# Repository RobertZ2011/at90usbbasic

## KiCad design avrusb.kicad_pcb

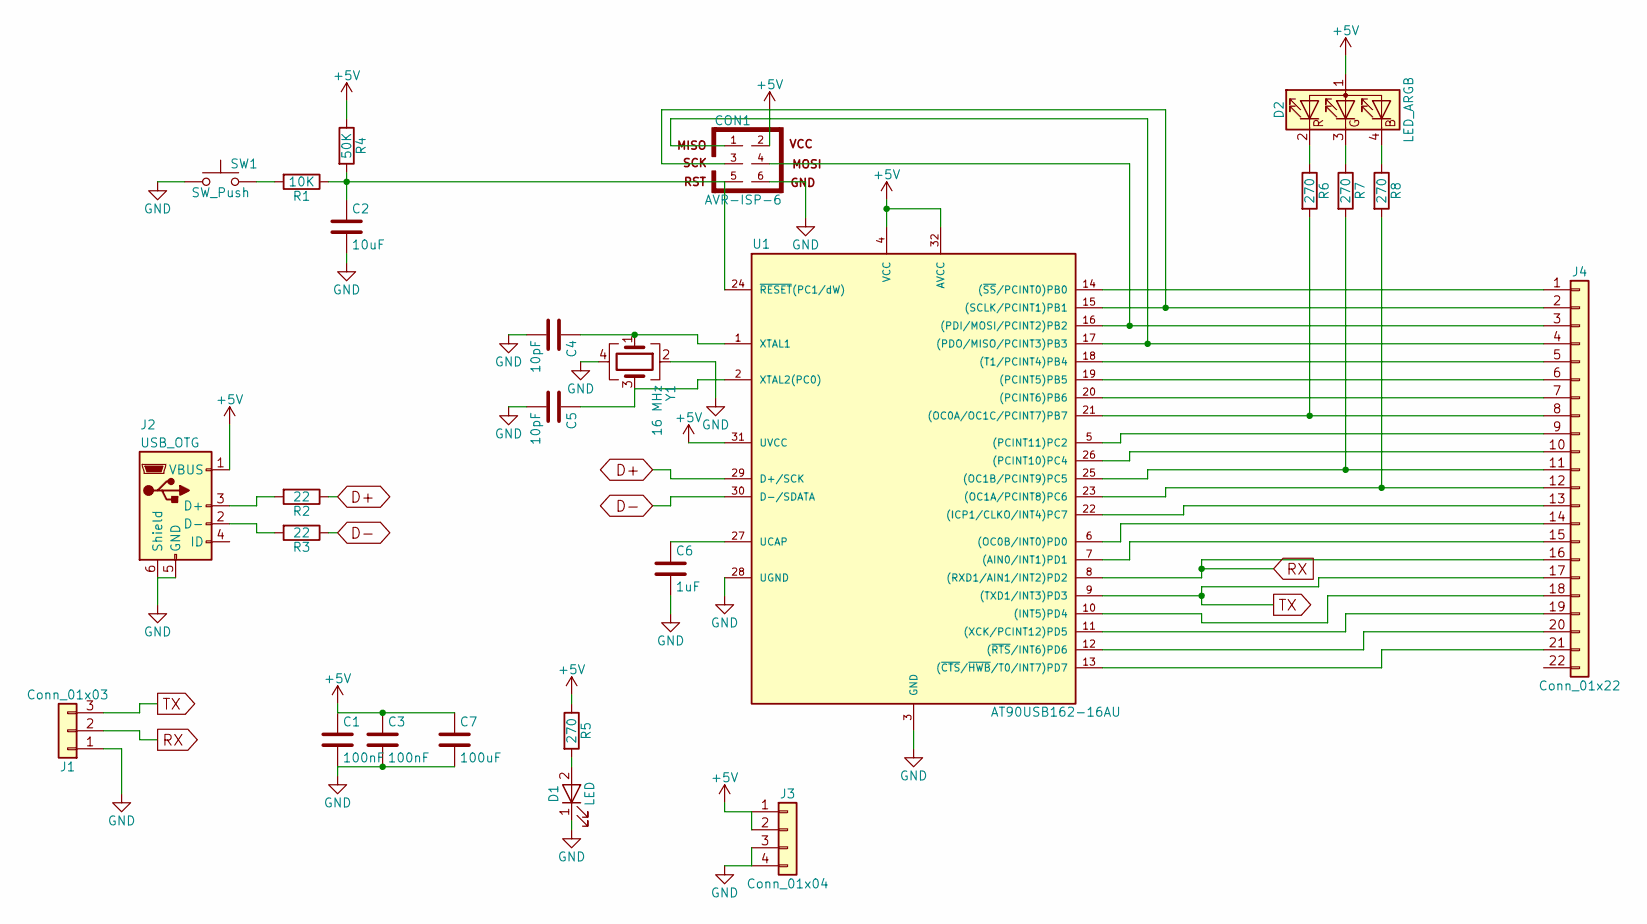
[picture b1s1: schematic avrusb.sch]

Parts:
C1, C3: 100nF; C_0805_HandSoldering
C2: 10uF; C_1206_HandSoldering
C4, C5: 10pF; C_0805_HandSoldering
C6: 1uF; C_1206_HandSoldering
C7: 100uF; CP_Elec_5x5.3
CON1: AVR-ISP-6; Pin_Header_Straight_2x03_Pitch2.54mm
D1: LED; LED_0805_HandSoldering
D2: LED_ARGB; LED_Cree-PLCC4_3.2x2.8mm_CCW
J1: Conn_01x03; Pin_Header_Straight_1x03_Pitch2.54mm
J2: USB_OTG; USB_Micro-B_Molex-105017-0001
J3: Conn_01x04; Pin_Header_Straight_1x04_Pitch2.54mm
J4: Conn_01x22; Pin_Header_Straight_2x11_Pitch2.54mm
R1: 10K; R_0805_HandSoldering
R2, R3: 22; R_0805_HandSoldering
R4: 50K; R_0805_HandSoldering
R5, R6, R7, R8: 270; R_0805_HandSoldering
SW1: SW_Push; SW_SPST_B3S-1000
U1: AT90USB162-16AU; TQFP-32_7x7mm_Pitch0.8mm
Y1: 16 MHz; Crystal_SMD_3225-4pin_3.2x2.5mm_HandSoldering

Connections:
D+: R2.1, U1.29 (D+/SCK)
D-: R3.1, U1.30 (D-/SDATA)
GND: C1.2, C2.2, C3.2, C4.2, C5.2, C6.2, C7.2, CON1.6, D1.1 (K), J1.1, J2.5 (GND), J2.6 (Shield), J3.3, J3.4, SW1.1, U1.3 (GND), U1.28 (UGND), Y1.2, Y1.4
unnamed: C2.1, CON1.5, R1.1, R4.2, U1.24 (~RESET~(PC1/dW))
unnamed: C4.1, U1.1 (XTAL1), Y1.1
unnamed: C5.1, U1.2 (XTAL2(PC0)), Y1.3
unnamed: C6.1, U1.27 (UCAP)
unnamed: CON1.1, J4.4, U1.17 ((PDO/MISO/PCINT3)PB3)
unnamed: CON1.4, J4.3, U1.16 ((PDI/MOSI/PCINT2)PB2)
unnamed: D1.2 (A), R5.2
unnamed: D2.2 (RK), R6.1
unnamed: D2.3 (GK), R7.1
unnamed: D2.4 (BK), R8.1
unnamed: J2.2 (D-), R3.2
unnamed: J2.3 (D+), R2.2
unnamed: J4.1, U1.14 ((~SS~/PCINT0)PB0)
unnamed: J4.5, U1.18 ((T1/PCINT4)PB4)
unnamed: J4.6, U1.19 ((PCINT5)PB5)
unnamed: J4.7, U1.20 ((PCINT6)PB6)
unnamed: J4.8, R6.2, U1.21 ((OC0A/OC1C/PCINT7)PB7)
unnamed: J4.9, U1.5 ((PCINT11)PC2)
unnamed: J4.10, U1.26 ((PCINT10)PC4)
unnamed: J4.11, R7.2, U1.25 ((OC1B/PCINT9)PC5)
unnamed: J4.12, R8.2, U1.23 ((OC1A/PCINT8)PC6)
unnamed: J4.13, U1.22 ((ICP1/CLKO/INT4)PC7)
unnamed: J4.14, U1.6 ((OC0B/INT0)PD0)
unnamed: J4.15, U1.7 ((AIN0/INT1)PD1)
unnamed: J4.18, U1.10 ((INT5)PD4)
unnamed: J4.19, U1.11 ((XCK/PCINT12)PD5)
unnamed: J4.20, U1.12 ((~RTS~/INT6)PD6)
unnamed: J4.21, U1.13 ((~CTS~/~HWB~/T0/INT7)PD7)
unnamed: R1.2, SW1.2
RX: J1.2, J4.16, U1.8 ((RXD1/AIN1/INT2)PD2)
TX: J1.3, J4.17, U1.9 ((TXD1/INT3)PD3)

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
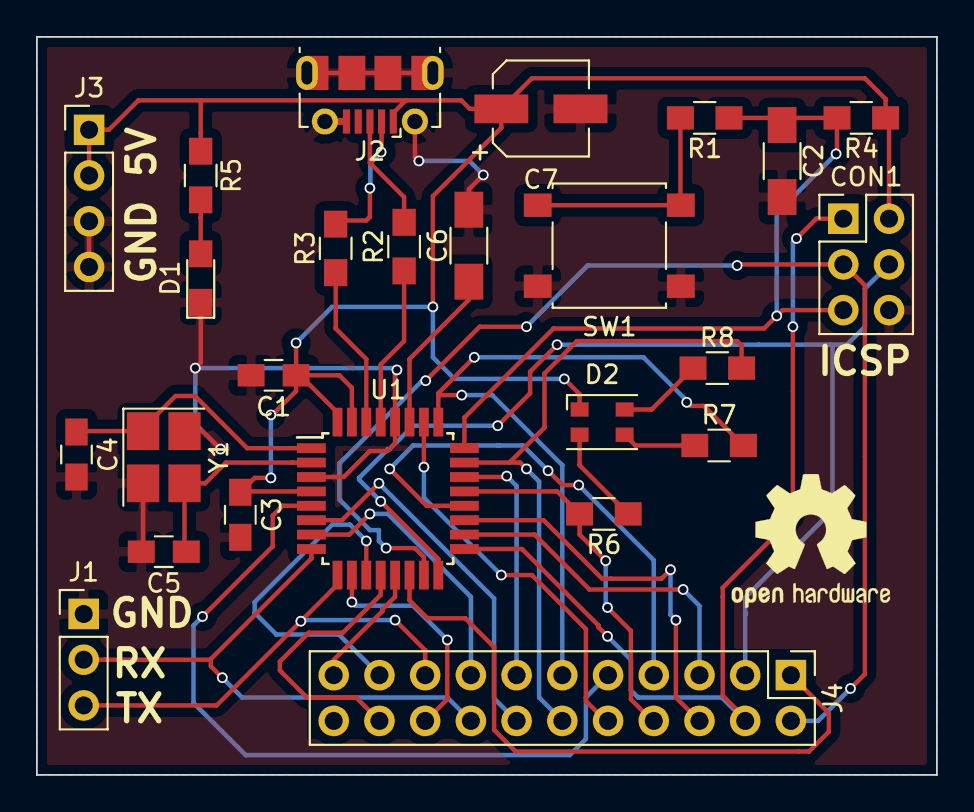
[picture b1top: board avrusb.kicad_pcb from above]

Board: 2 copper layers, 50.0 x 41.0 mm, 25 parts (0 on the bottom side), 36 nets.

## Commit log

2017-11-23 Initial commit, most work done
2017-11-23 Added github url
